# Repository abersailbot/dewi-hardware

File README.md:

# dewi-hardware
Hardware designs and issue tracking for Dewi.

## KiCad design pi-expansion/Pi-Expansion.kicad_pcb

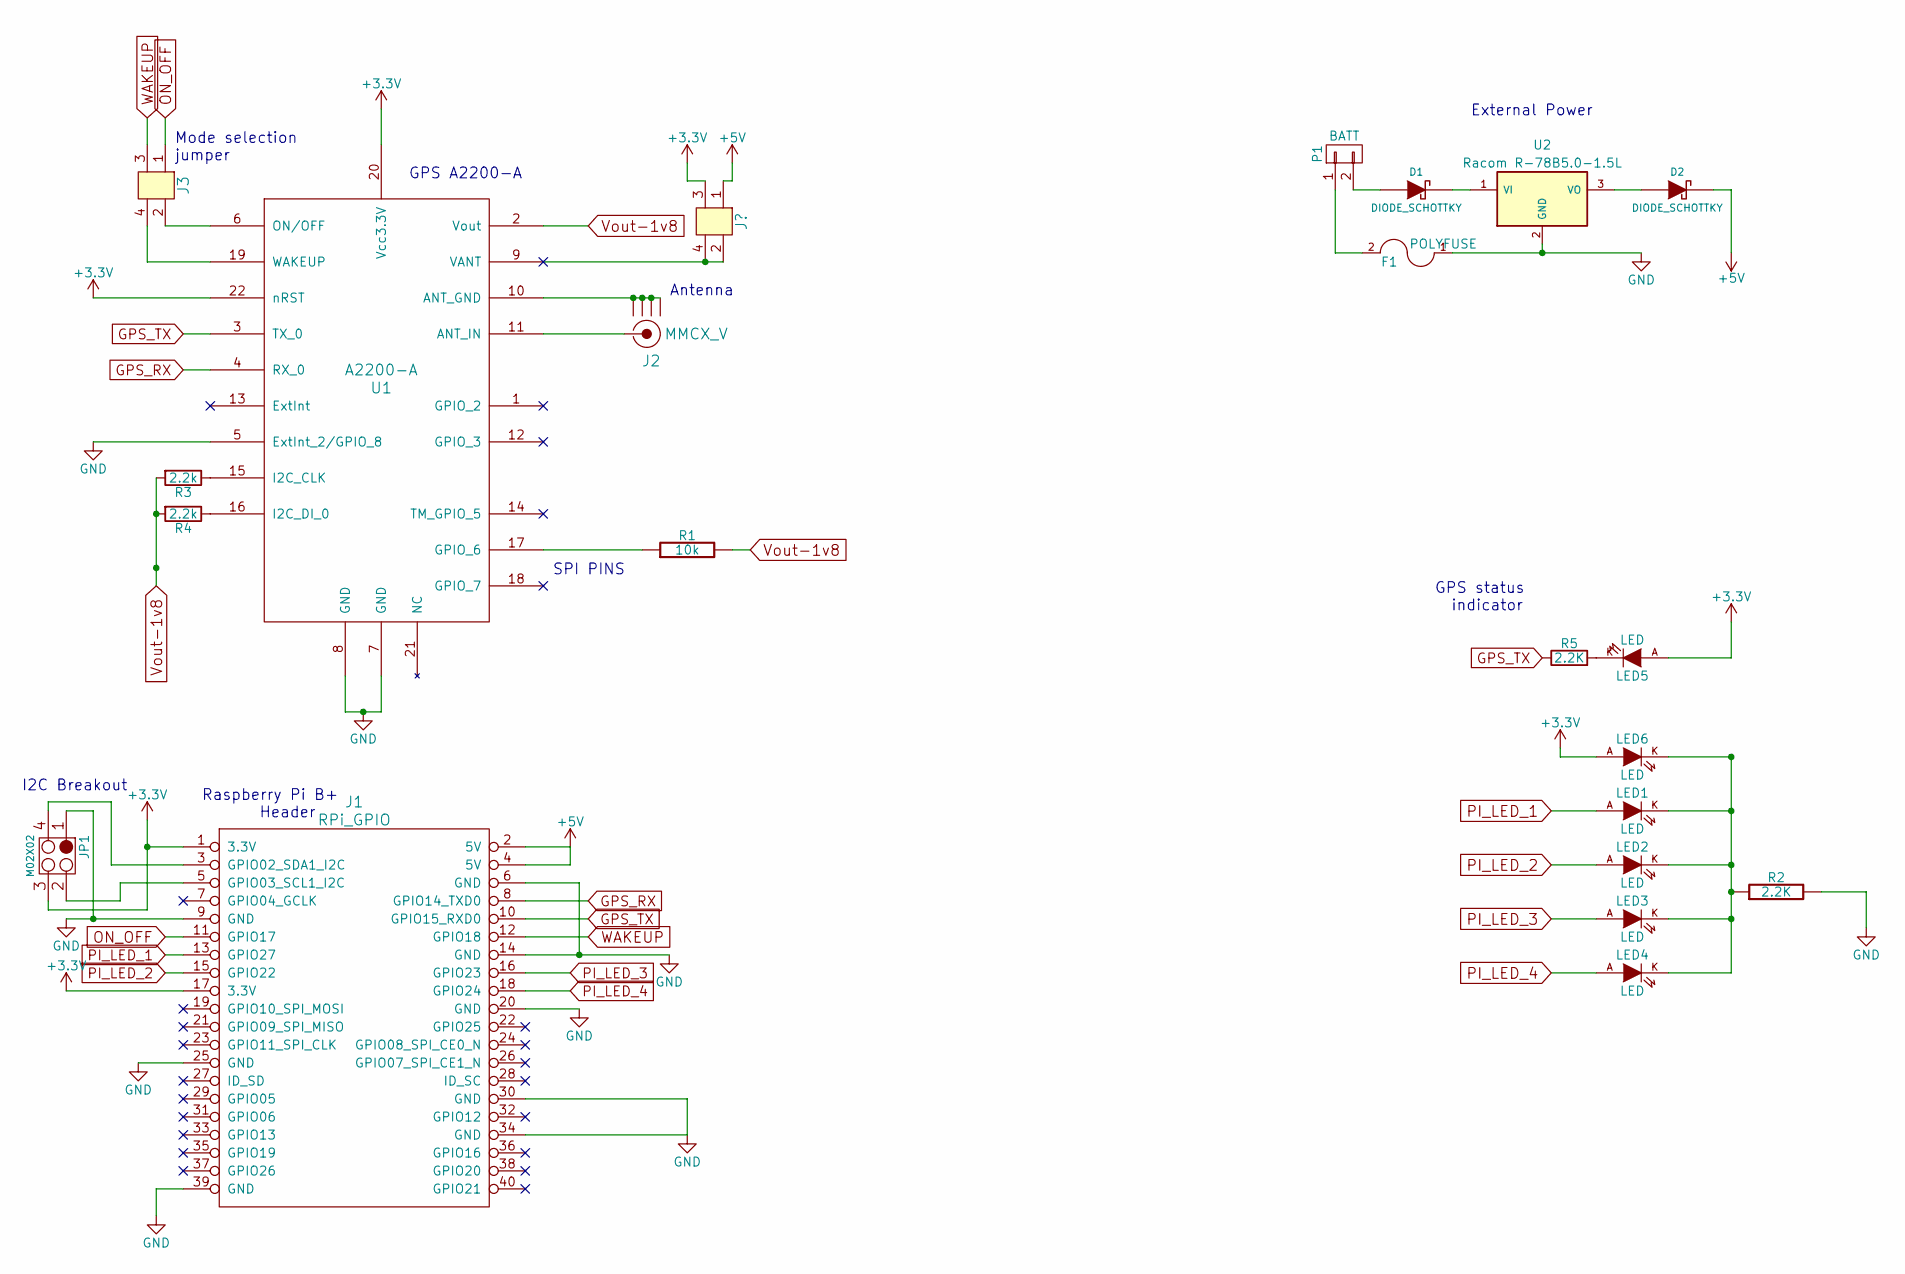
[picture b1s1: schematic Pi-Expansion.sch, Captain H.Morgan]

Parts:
D1, D2: DIODE_SCHOTTKY; SOD-323
F1: POLYFUSE; Fuse_SMD1206_HandSoldering
J1: RPi_GPIO; Pin_Header_Straight_2x20
J2: MMCX_H; MMCX_V; Manufacturer Part Number 142-0711-821
J3: PINHEADER_2X2_SMD; Pinhead_2x2_SMD; Manufacturer Part Number 0015912040
JP1: M02X02; Socket_MOLEX-KK-RM2-54mm_Lock_4pin_straight
LED1, LED2, LED3, LED4, LED5, LED6: LED; LED-1206
P1: BATT; Socket_MOLEX-KK-RM2-54mm_Lock_2pin_straight
R1: 10k; 1206
R2, R5: 2.2K; 1206
R3, R4: 2.2k; 1206
U1: A2200-A
U2: Racom R-78B5.0-1.5L; DCDC-Conv_Recom_R-78HBxx-0.5

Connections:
+3V3: J1.1 (3.3V), J1.17 (3.3V), JP1.3, LED5.A, LED6.A, U1.20 (Vcc3.3V), U1.22 (nRST); also elsewhere on the board
+5V: D2.K, J1.2 (5V), J1.4 (5V); also elsewhere on the board
GND: F1.1, J1.6 (GND), J1.9 (GND), J1.14 (GND), J1.20 (GND), J1.25 (GND), J1.30 (GND), J1.34 (GND), J1.39 (GND), JP1.1, R2.2, U1.5 (ExtInt_2/GPIO_8), U1.7 (GND), U1.8 (GND), U2.2 (GND)
GPS_RX: J1.8 (GPIO14_TXD0), U1.4 (RX_0)
GPS_TX: J1.10 (GPIO15_RXD0), R5.1, U1.3 (TX_0)
unnamed: D1.A, P1.2
unnamed: D1.K, U2.1 (VI)
unnamed: D2.A, U2.3 (VO)
unnamed: F1.2, P1.1
unnamed: J1.3 (GPIO02_SDA1_I2C), JP1.4
unnamed: J1.5 (GPIO03_SCL1_I2C), JP1.2
unnamed: J2.1 (RF), U1.11 (ANT_IN)
unnamed: J2.2 (GND1), J2.3 (GND2), J2.4 (GND3), J2.5 (GND4), U1.10 (ANT_GND)
unnamed: J3.2, U1.6 (ON/OFF)
unnamed: J3.4, U1.19 (WAKEUP)
unnamed 15: U1.9 (VANT); also elsewhere on the board
unnamed: LED1.K, LED2.K, LED3.K, LED4.K, LED6.K, R2.1
unnamed: LED5.K, R5.2
unnamed: R1.1, U1.17 (GPIO_6)
unnamed: R3.1, U1.15 (I2C_CLK)
unnamed: R4.1, U1.16 (I2C_DI_0)
ON_OFF: J1.11 (GPIO17), J3.1
PI_LED_1: J1.13 (GPIO27), LED1.A
PI_LED_2: J1.15 (GPIO22), LED2.A
PI_LED_3: J1.16 (GPIO23), LED3.A
PI_LED_4: J1.18 (GPIO24), LED4.A
Vout-1v8: R1.2, R3.2, R4.2, U1.2 (Vout)
WAKEUP: J1.12 (GPIO18), J3.3

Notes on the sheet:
SPI PINS
Mode selection jumper
GPS A2200-A
I2C Breakout
External Power
GPS status indicator
Raspberry Pi B+ Header
Antenna

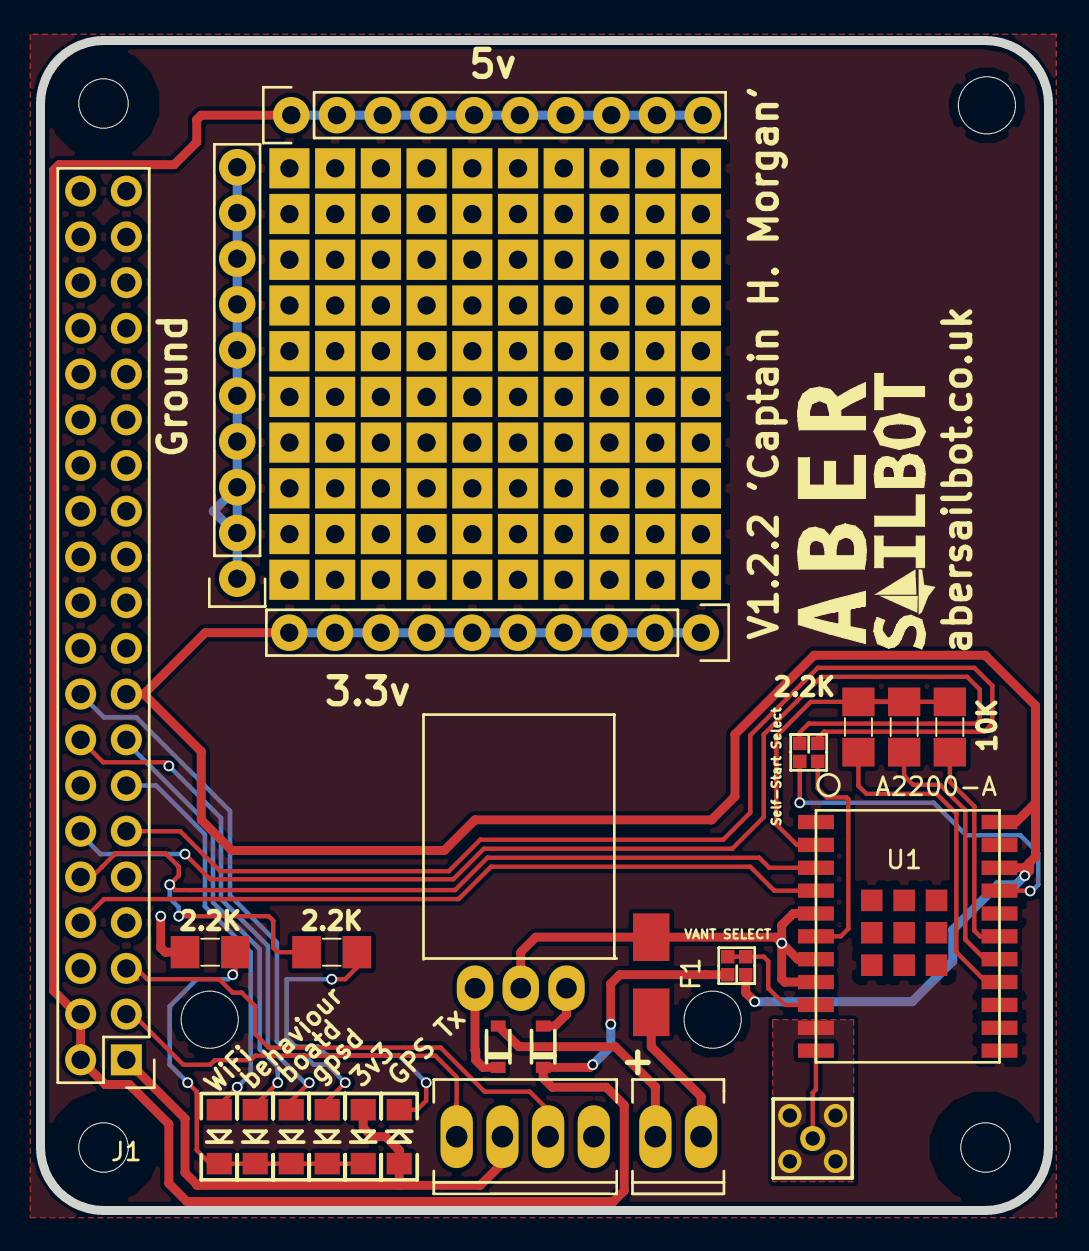
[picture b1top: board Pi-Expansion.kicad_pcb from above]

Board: 2 copper layers, 56.0 x 65.0 mm, 27 parts (0 on the bottom side), 28 nets.

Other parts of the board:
1111, 1112, 1121: RPi_Hat_Mounting_Hole
ARDUINO_SHIELD: val**; ARDUINO_SHIELD_3_HOLE
J4: PINHEADER_2X2_SMD; 2-WAY-SMD-JUMPER
svg2mod: G***; Sailbot_Logo

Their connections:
+3V3: J4.3; also elsewhere on the board
+5V: J4.1; also elsewhere on the board
unnamed 15: J4.2, J4.4; also elsewhere on the board

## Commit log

2015-10-01 wiring diagram for the Dewi electronics
    fairly self explanatory
2015-10-01 adding a image of a basic sketch for the dewi wiring diagram
2015-10-01 manually adding as pull request screwed up
2015-10-01 removed the dodgy wiring diagram file
2016-01-27 Add small hardware spec document
2016-01-27 Fix embarrassing typo
2016-01-27 Add blank wiring document
2016-01-27 Add wiring standard (from abersailbot/management)
2016-02-01 add basic project files for kicad and first library for freetronics
2016-02-14 Finalised Kicad librarys for A2200-A, myriadrf, and pi_Hat, also layout for first draft of Schmatic
2016-02-14 Rejigged librarys abit to be less random, made sure to use submodules instead of local copys. Also did first draft of pcb layout
2016-02-14 Rename Pi-Expansion -> pi-expansion
    Lower case names are nicer to deal with.
2016-02-15 added custom library for arduino board with only mounting holes, also added in the hole position for ardino, and refined pcb outline
2016-02-15 fixed board outline, moved gps
2016-02-16 did a full layout of the pcb, should be pretty much compleat, also fixed yet more issues librarys
2016-02-16 add copper fill for ground plane, and second mill revisions for prototyping
2016-05-10 Use https links for git submodules
    Travis freaks out with ssh keys.
2016-05-16 Updated 3v3 and Gnd tabs on pi header on schmatic
2016-05-16 Adds reverse voltage protection for DC-DC converter allowing for safe operation of pi form UUSB connector
2016-05-16 Updated layout around gps, reconfigured for autowakeup and NMEA at 4800.
2016-05-16 minor tweaks, and rotated pi header, removed infill and traces
2016-05-19 Made minor tweaks to schematic layout, updated footprints and tweaked pcb layout
2016-05-19 First draft pcb layout, most tracks in place, footprints in near final positions
2016-05-19 Final Layout, Traces and footprints in place, added GPS_TX sensing circuit 3.3v powerled.
2016-05-20 updated power footprints, minor tweaks
2016-05-21 Add license
2016-05-22 Silk screen update, nudged some footprints for better flow.
2016-05-22 Final Commit for V1.2 'Captain H.Morgan', all planes, solder masks, and components in final places.
2016-05-22 Documentation update, added notes to schematic.
2016-05-22 Documentation tweaks
2016-05-22 Updated GPS ground Pads
2016-05-23 updateded fab files with ground plane fix
2016-06-17 made minor mods to power supply including moving reverse protection diode from negitive side to positive side to reduce voltage drop.
2016-06-17 minor tweaks to in fill
2016-06-18 cleared out fabrication files as they should be generated fresh when needed, also simplified circuitry for the tx sense led
2016-06-18 Added current limiting resistor for GPS TX indicator, also fiddled with Copper fill
2016-06-18 updated led resistor placement so they no longer obstruct the legand on the silk screen
2016-06-30 Final version sent to fab, retraced GPS_TX to fix net issue between 2k2 resistor and pi header
2016-09-07 Added voltage select jumper to VANT.
2016-10-16 Added voltage select for GPS Vant between 5v and 3v3.
2016-11-21 Updated silkscreen typo.
2016-11-21 Nudged silkscreen for @tomgc96
2016-11-21 moved url to silkscreen and updated it for .co.uk address
2016-11-21 Moved led vias and traces to clear around silkscreen.
2016-11-21 de-capitalised gpsd
2016-11-25 Moved captian morgan files to seperate repo and removed copies in this repo. all files related to captain morgan can now be found in: https://github.com/abersailbot/Captain-H-Morgan
2016-11-25 Updated the wiring standard to inclued infomation about current handeling, and servo wiring
2016-11-25 moved wiring standard to docs repo.
